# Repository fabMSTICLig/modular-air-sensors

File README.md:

Modular Air Sensor MAS
===========

This is an application to build device with modular air sensors using the [RIOT-OS](https://www.riot-os.org/) middleware.

The project is based on the LORA E5 mini board of seeed studio https://wiki.seeedstudio.com/LoRa_E5_mini/

Usage
=====

## Dependecies

- RIOT-OS https://github.com/RIOT-OS/RIOT
- DLPP https://github.com/fabMSTICLig/dlpp
- Sensirion riot external drivers https://github.com/fabMSTICLig/riot-sensirion-modules

In the Makefile you can enable wich sensor you want to use and define for each of them a channel and a sampling interval.

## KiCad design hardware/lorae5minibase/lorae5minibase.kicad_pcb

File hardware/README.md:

#Hardware

This forlder contain a KICAD 6 project of the lora e5 mini base board and a SVG file for laser cutting the standing sensors holder.

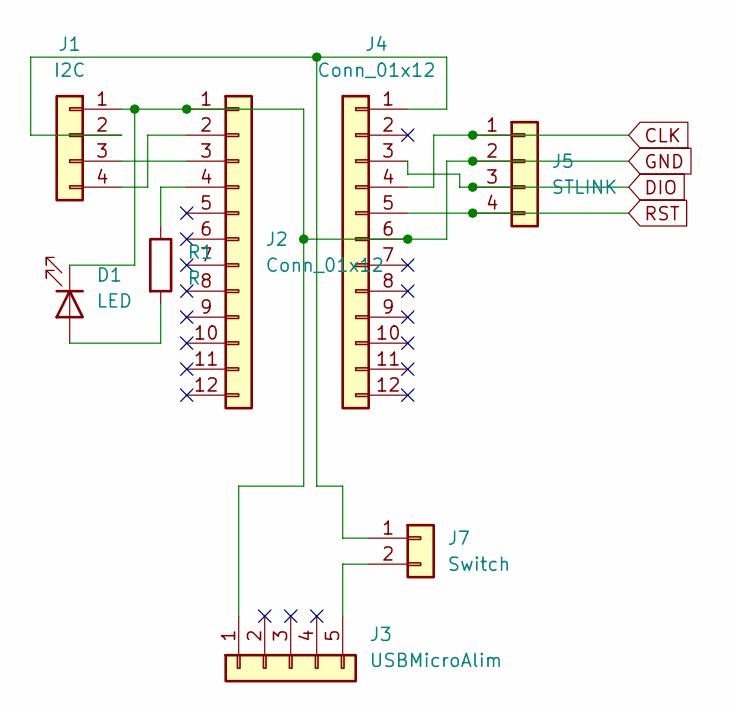
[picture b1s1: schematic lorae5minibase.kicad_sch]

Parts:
D1: LED; PinHeader_1x02_P2.54mm_Vertical
J1: I2C; PinHeader_1x04_P2.00mm_Vertical
J2, J4: Conn_01x12; PinHeader_1x12_P2.54mm_Vertical
J3: USBMicroAlim; PinHeader_1x05_P2.54mm_Vertical
J5: STLINK; PinHeader_1x04_P2.54mm_Vertical
J7: Switch; PinHeader_1x02_P2.54mm_Vertical
R1: R; PinHeader_1x02_P2.54mm_Vertical

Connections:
CLK: J4.4, J5.1
DIO: J4.3, J5.3
GND: D1.1 (K), J1.1, J2.1, J3.1, J4.6, J5.2
unnamed: J1.2, J4.1, J7.1
unnamed: J1.3, J2.3
unnamed: J1.4, J2.2
unnamed: J2.4, R1.1
unnamed: J3.5, J7.2
unnamed: D1.2 (A), R1.2
RST: J4.5, J5.4

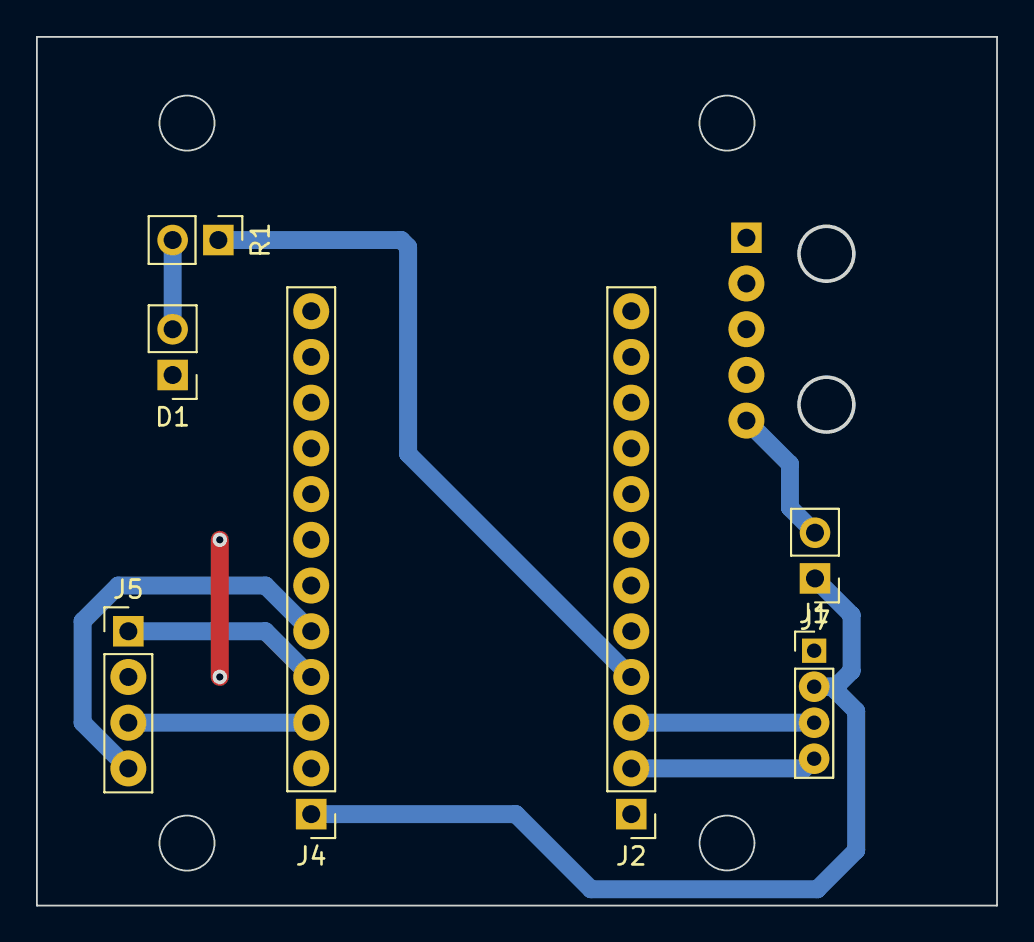
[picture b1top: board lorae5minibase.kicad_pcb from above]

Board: 2 copper layers, 53.2 x 48.2 mm, 8 parts (1 on the bottom side), 10 nets.

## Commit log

2022-09-28 add LICENCE
2022-09-28 Add picture a device
2022-09-28 reduce image
2022-10-13 Add raw of sen5X and fix old airqual -> mas include
2024-05-22 add support SEN55 and watchdog
